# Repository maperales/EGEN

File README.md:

Archivos del regulador de temperatura. Electrónica General 2ºGITI Universidad de Sevilla.
=========================================================================================
En este repositorio se pueden encontrar todos los archivos necesarios para replicar el proyecto llevado a cabo en la parte 4 de la asignatura Electrónica General, de 2º curso del Grado de Ingeniera de las Tecnologías Industriales, de la Universidad de Sevilla.
  - EAGLE: archivos de Eagle para realizar la placa
  - ENERGIA: programas en energía con la funcionalidad desarrollada

En los sucesivos directorios se pueden encontrar las versiones de la placa hechas cada curso, junto con la versión del código, en caso de cambios en el código.

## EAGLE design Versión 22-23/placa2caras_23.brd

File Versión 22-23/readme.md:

Nuevas versiones de la placa y del sw
=====================================
En este directorio encontraréis los ficheros del diseño realizado el curso 2022/23.

Básicamente, el cambio fundamental respecto al curso pasado es el valor (y el nombre) de las resistencias de la adaptación analógica, para ajustar al nuevo valor de la NTC utilizada (con un valor de B diferente de la de cursos anteriores). Igualmente, se han cambiado los valores de la tabla precalculada de temperatura en función del valor de ADC, para ajustar la nueva recta. Los cambios son pequeños, pero significativos.

A modo de resumen:
  - **placa2caras_23.brd**: trazado básico de pistas del diseño a partir del esquema
  - **placa2caras_23.sch**: esquema del diseño realizado
  - **placa2caras_CTO4_2023.json**: trazado de pistas definitivo, en EasyEDA, con los logos y demás.
  - **PBL_CAL.INO**: programa para calibrar la placa
  - **PBL.INO / PBL.h**: programa y librería para programar finalmente la placa

**Muy Importante: recuerda que para poder programar la placa deberás seguir los pasos que se indican en el directorio [https://github.com/maperales/EGEN/tree/master/ENERGIA]**

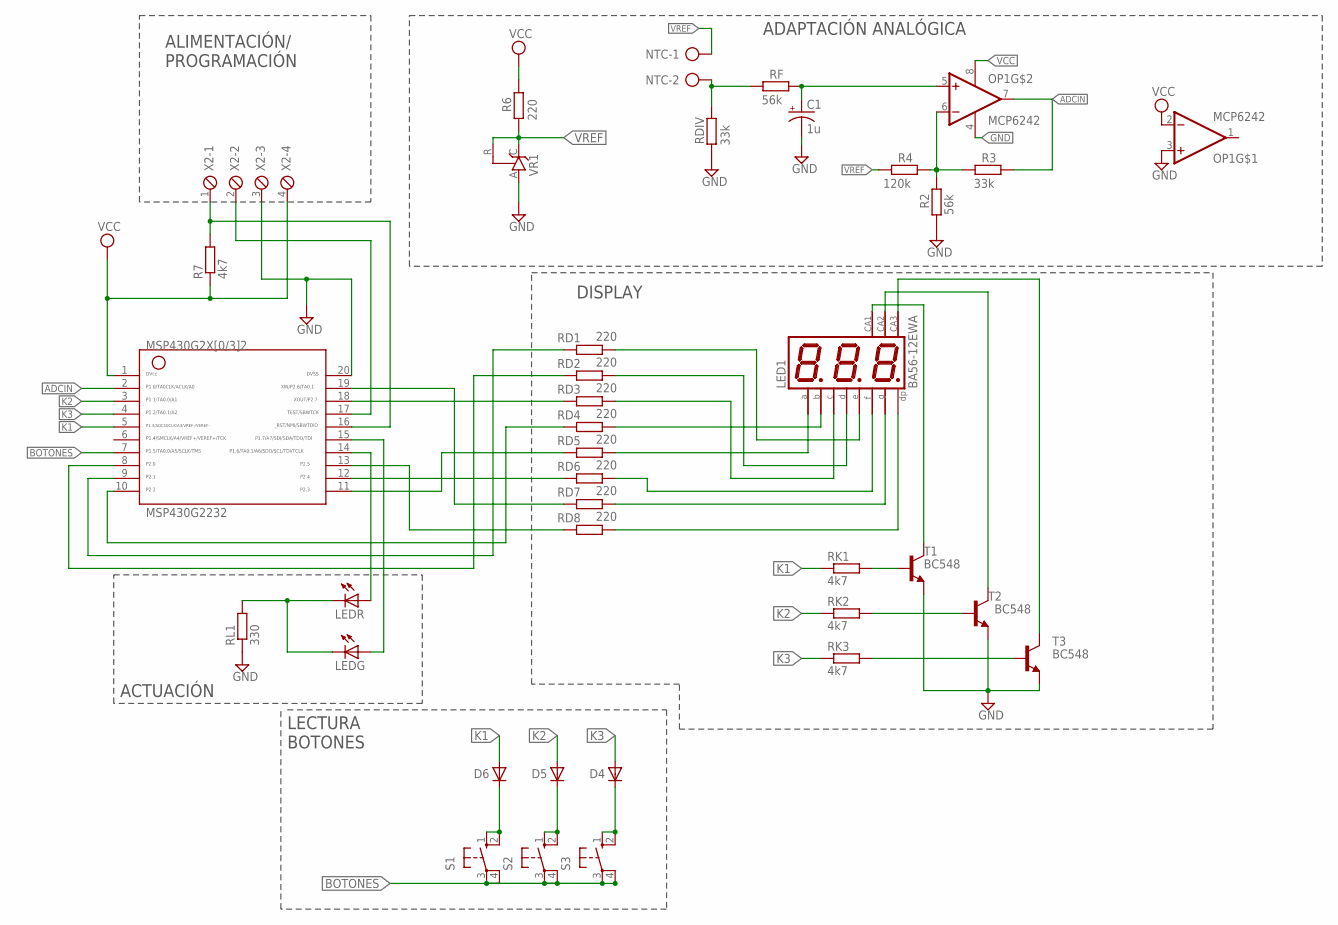
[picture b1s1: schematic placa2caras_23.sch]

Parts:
C1: 1u; E2,5-6E
D4, D5, D6: 1N4148DO35-10; DO35-10
LED1: BA56-12EWA; BX56-12
LEDG: LED5MM
LEDR: LED5MM
MSP430G2232: G2X[0/3]2---N20; N20
NTC: AK500/2
OP1: MCP6242; DIL8_MOD
R2: 56k; 0207/10
R3: 33k; 0207/10
R4: 120k; 0207/10
R6: 220; 0207/10
R7: 4k7; 0207/10
RD1, RD2, RD3, RD4, RD5, RD6, RD7, RD8: 220; 0207/10
RDIV: 33k; 0207/10
RF: 56k; 0207/10
RK1, RK2, RK3: 4k7; 0207/10
RL1: 330; 0207/10
S1, S2, S3: 10-XX; B3F-10XX
T1, T2, T3: BC548; TO92-EBC
VR1: TL431CLP; TO92-CLP
X2: MPT4; 4POL254

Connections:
ADCIN: MSP430G2232.2, OP1.7 (OUT), R3.1
BOTONES: MSP430G2232.7, S1.3, S1.4 (P1), S2.3, S2.4 (P1), S3.3, S3.4 (P1)
GND: C1.-, MSP430G2232.20, OP1.3 (+IN), OP1.4 (V-), R2.1, RDIV.2, RL1.1, T1.E, T2.E, T3.E, VR1.A, X2.3
K1: D6.A, MSP430G2232.5, RK1.1
K2: D5.A, MSP430G2232.3, RK2.1
K3: D4.A, MSP430G2232.4, RK3.1
unnamed: RK1.2, T1.B
unnamed: RK2.2, T2.B
unnamed: RK3.2, T3.B
unnamed: LED1.11 (A), RD5.2
unnamed: LED1.1 (E), RD1.2
unnamed: LED1.2 (D), RD2.2
unnamed: LED1.4 (C), RD3.2
unnamed: LED1.7 (B), RD4.2
unnamed: LED1.10 (F), RD6.2
unnamed: LED1.5 (G), RD7.2
unnamed: MSP430G2232.17, X2.2
unnamed: LED1.3 (DP), RD8.2
unnamed: OP1.6 (-IN), R2.2, R3.2, R4.2
unnamed: LED1.12 (CA), T1.C
unnamed: NTC.2, RDIV.1, RF.2
unnamed: LED1.9 (CA), T2.C
unnamed: C1.+, OP1.5 (+IN), RF.1
unnamed: LED1.8 (CA), T3.C
unnamed: LEDG.K (C), LEDR.K (C), RL1.2
unnamed: MSP430G2232.16, R7.2, X2.1
unnamed: MSP430G2232.19, RD7.1
unnamed: MSP430G2232.18, RD3.1
unnamed: MSP430G2232.13, RD8.1
unnamed: MSP430G2232.12, RD6.1
unnamed: MSP430G2232.11, RD5.1
unnamed: MSP430G2232.10, RD4.1
unnamed: MSP430G2232.9, RD1.1
unnamed: MSP430G2232.8, RD2.1
unnamed: D5.C, S2.1 (S), S2.2 (S1)
unnamed: D4.C, S3.1 (S), S3.2 (S1)
unnamed: D6.C, S1.1 (S), S1.2 (S1)
unnamed: LEDG.A, MSP430G2232.15
unnamed: LEDR.A, MSP430G2232.14
VCC: MSP430G2232.1, OP1.2 (-IN), OP1.8 (V+), R6.1, R7.1, X2.4
VREF: NTC.1, R4.1, R6.2, VR1.C, VR1.R

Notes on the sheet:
ADAPTACIÓN ANALÓGICA
DISPLAY
LECTURA BOTONES
ACTUACIÓN
ALIMENTACIÓN/ PROGRAMACIÓN

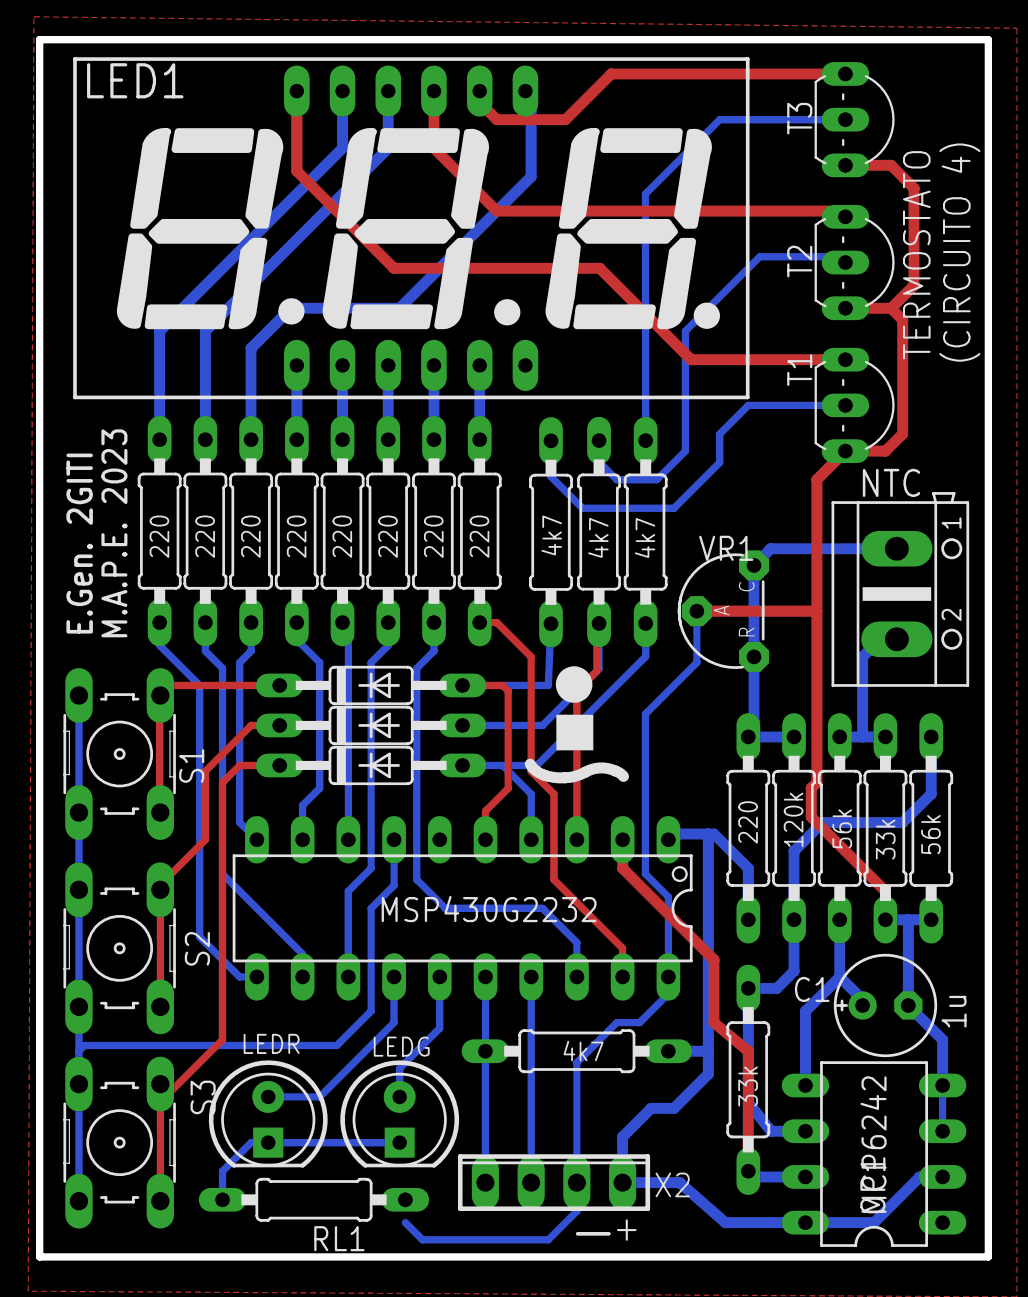
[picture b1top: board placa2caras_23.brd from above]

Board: 2 copper layers, 52.7 x 67.6 mm, 37 parts (0 on the bottom side), 41 nets.

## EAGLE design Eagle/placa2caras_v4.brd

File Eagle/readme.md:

Versión actual de los archivos de Eagle de la placa
==================================================
La placa está fabricada a doble cara, con taladros metalizados y un ancho de pista estndar de 16mils. En estas condiciones, resulta 
un poco compleja de fabricar con métodos *artesanales*. Los ficheros incluidos son:
- placa2caras_v1718.sch: esquema de la placa
- placa2caras_v1718.brd: rutado de la placa
- placa2caras_v1718_TOP.pdf: impresión de la cara superior, en pdf sin escalar ni hacer *mirror*.
- placa2caras_v1718_BOTT.pdf: impresión de la cara inferior, en pdf, sin escalar pero con  *mirror*
- placa2caras_v1718_TSILK.pdf: serigrafía de la cara superior, en pdf sin escalar ni hacer *mirror*.
- placa2caras_v1718_BSILK.pdf: serigrafí de la cara inferior, en pdf, sin escalar pero con  *mirror*
- - -
Las resistencias RD1..RD8 aparecen en el esquema como resistencias de 220 ohmios, aunque se pueden usar de 100 ohmios.

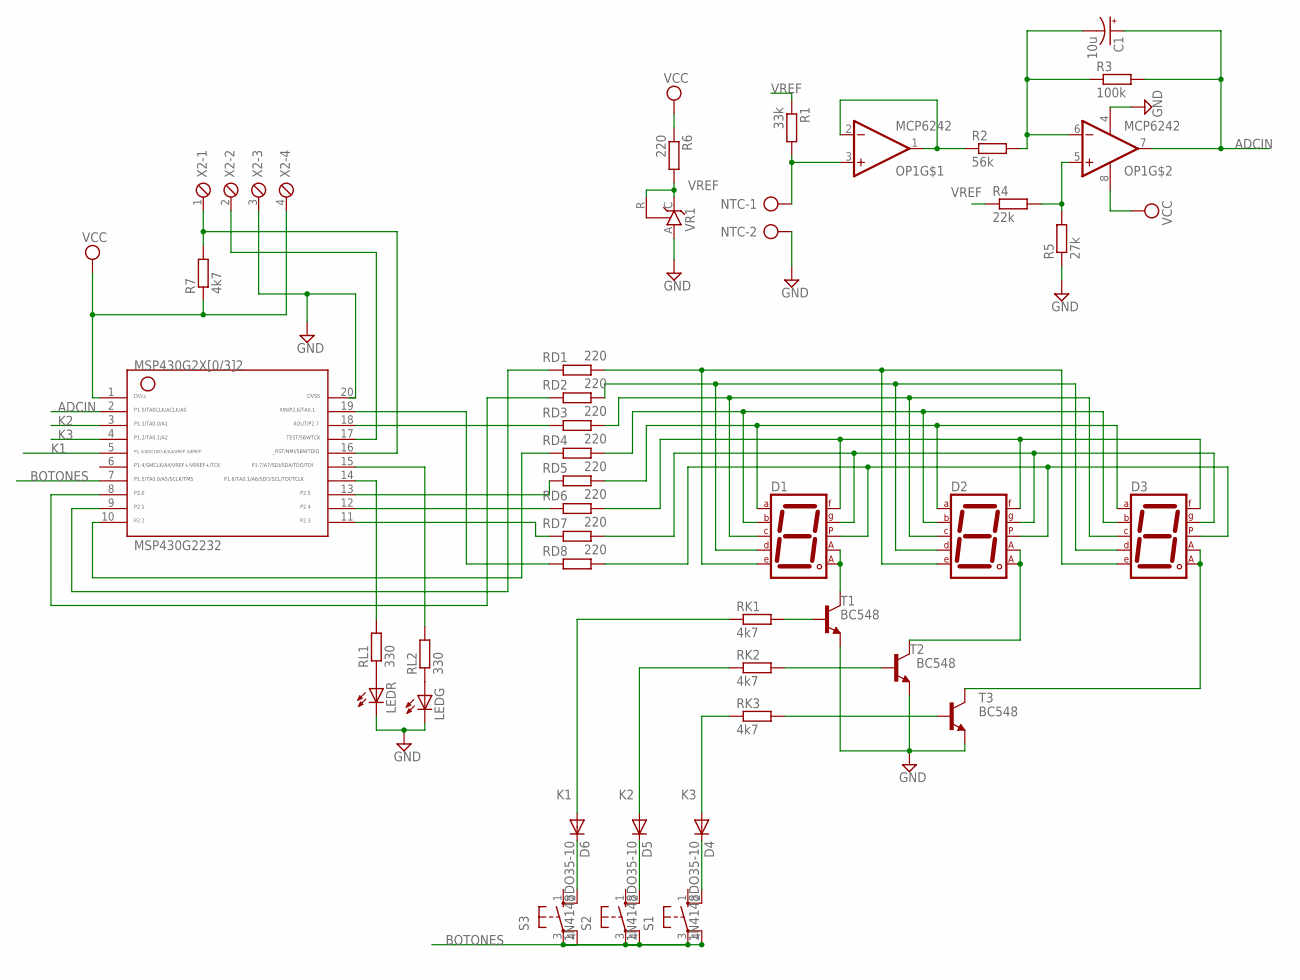
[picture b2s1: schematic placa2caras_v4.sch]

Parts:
C1: 10u; E2,5-6E
D1, D2, D3: 7SEG-CA; 7SEG-13
D4, D5, D6: 1N4148DO35-10; DO35-10
LEDG: LED5MM
LEDR: LED5MM
MSP430G2232: G2X[0/3]2---N20; N20
NTC: AK500/2
OP1: MCP6242; DIL8_MOD
R1: 33k; 0207/10
R2: 56k; 0207/10
R3: 100k; 0207/10
R4: 22k; 0207/10
R5: 27k; 0207/10
R6: 220; 0207/10
R7: 4k7; 0207/10
RD1, RD2, RD3, RD4, RD5, RD6, RD7, RD8: 220; 0207/10
RK1, RK2, RK3: 4k7; 0207/10
RL1, RL2: 330; 0207/10
S1, S2, S3: 10-XX; B3F-10XX
T1, T2, T3: BC548; TO92-EBC
VR1: TL431CLP; TO92-CLP
X2: MPT4; 4POL254

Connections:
ADCIN: C1.+, MSP430G2232.2, OP1.7 (OUT), R3.2
BOTONES: MSP430G2232.7, S1.3, S1.4 (P1), S2.3, S2.4 (P1), S3.3, S3.4 (P1)
GND: LEDG.K (C), LEDR.K (C), MSP430G2232.20, NTC.2, OP1.4 (V-), R5.1, T1.E, T2.E, T3.E, VR1.A, X2.3
K1: D6.A, MSP430G2232.5, RK1.1
K2: D5.A, MSP430G2232.3, RK2.1
K3: D4.A, MSP430G2232.4, RK3.1
unnamed: RK1.2, T1.B
unnamed: RK2.2, T2.B
unnamed: RK3.2, T3.B
unnamed: D1.7 (A), D2.7 (A), D3.7 (A), RD5.2
unnamed: D1.3 (CA1), D1.8 (CA2), T1.C
unnamed: D1.6 (B), D2.6 (B), D3.6 (B), RD4.2
unnamed: D2.3 (CA1), D2.8 (CA2), T2.C
unnamed: D1.4 (C), D2.4 (C), D3.4 (C), RD3.2
unnamed: D3.3 (CA1), D3.8 (CA2), T3.C
unnamed: D1.2 (D), D2.2 (D), D3.2 (D), RD2.2
unnamed: MSP430G2232.17, X2.2
unnamed: D1.1 (E), D2.1 (E), D3.1 (E), RD1.2
unnamed: OP1.5 (+IN), R4.2, R5.2
unnamed: D1.9 (F), D2.9 (F), D3.9 (F), RD6.2
unnamed: NTC.1, OP1.3 (+IN), R1.2
unnamed: D1.10 (G), D2.10 (G), D3.10 (G), RD7.2
unnamed: OP1.1 (OUT), OP1.2 (-IN), R2.1
unnamed: D1.5 (DP), D2.5 (DP), D3.5 (DP), RD8.2
unnamed: C1.-, OP1.6 (-IN), R2.2, R3.1
unnamed: MSP430G2232.16, R7.2, X2.1
unnamed: MSP430G2232.19, RD8.1
unnamed: MSP430G2232.18, RD3.1
unnamed: MSP430G2232.13, RD5.1
unnamed: MSP430G2232.12, RD6.1
unnamed: MSP430G2232.11, RD7.1
unnamed: MSP430G2232.10, RD4.1
unnamed: MSP430G2232.9, RD1.1
unnamed: MSP430G2232.8, RD2.1
unnamed: D5.C, S2.2 (S1)
unnamed: D4.C, S1.2 (S1)
unnamed: D6.C, S3.2 (S1)
unnamed: MSP430G2232.15, RL2.2
unnamed: LEDR.A, RL1.1
unnamed: MSP430G2232.14, RL1.2
unnamed: LEDG.A, RL2.1
VCC: MSP430G2232.1, OP1.8 (V+), R6.1, R7.1, X2.4
VREF: R1.1, R4.1, R6.2, VR1.C, VR1.R

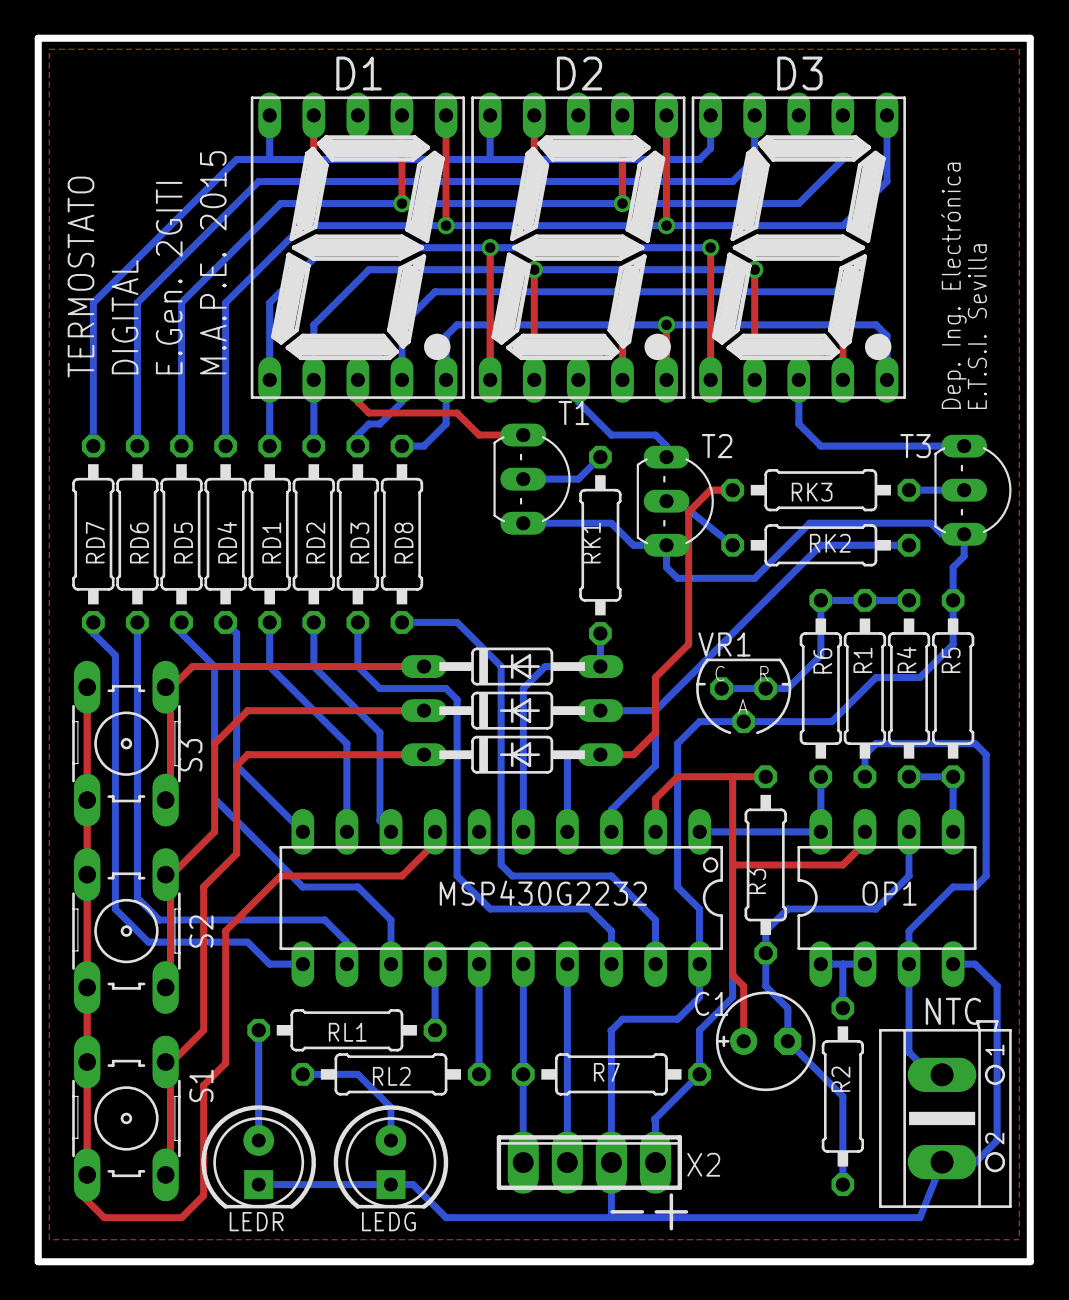
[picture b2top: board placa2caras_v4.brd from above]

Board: 2 copper layers, 57.1 x 70.5 mm, 40 parts (0 on the bottom side), 43 nets.

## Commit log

2017-03-21 Add files via upload
    Imagen de la conexión de la placa a un Launchpad para programarla
2025-04-29 Create CCS
